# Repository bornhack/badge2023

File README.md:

# BornHack 2023 NFC Badges

With this years badges, we are taking a look at NFC. There will be two badges, one that is a tag (using the NXP NTAG I2C Plus chip), and another with an NFC reader (using NXP PN7150), that can also do card emulation.

The reader badge sports an RP2040 dual core Cortex M0+ microcontroller from Raspberry Pi and 16MB of Quad SPI flash for code and data files, to handle USB connection and general application control.

The reader badge will come with [CircuitPython](https://circuitpython.org/) preloaded, for a very low barrier of entry, all you need is a USB-C cable, and your favorite text editor and you're ready for NFC hacking.

## CircuitPython restore file

If you flash the board with something else and want to get back to CircuitPython:
Bring the badge into the UF2 bootloader. This is done by holding the BOOT button and pressing RESET or by holding BOOT while powering on.
The badge will then show up as a mass storage device called something like RP2-?. This is the built in bootloader.
Then simply copy [firmware.uf2](https://github.com/bornhack/badge2023/raw/main/firmware.uf2) from the root of this repository.
The badge will reboot, and you are then back to CircuitPython.

CircuitPython supported with this board is found in the [circuitpython branch](https://github.com/bornhack/badge2023/tree/circuitpython)

The original python files that was on the badge when handed out are in the [cp-init branch](https://github.com/bornhack/badge2023/tree/cp-init)

## Designed in KiCad v7

To open the project, you will need to install a recent release version or one of the nightly builds, KiCad v5 or v6 won't open this design. The [reader schematic as a PDF](https://github.com/bornhack/badge2023/raw/main/nfc_reader/nfc_reader_schematics.pdf) and the [tag schematic as a PDF](https://github.com/bornhack/badge2023/raw/main/nfc_card_emulation_large/nfc_card_emulation_large_schematics.pdf) are included for reference.

Main Components:

- [Raspberry Pi SoC RP2040 - low-cost, high-performance microcontroller device](https://www.raspberrypi.com/documentation/microcontrollers/rp2040.html)
    - [datasheet](https://datasheets.raspberrypi.com/rp2040/rp2040-datasheet.pdf)
    - [RP2040 SDK Manuel](https://www.raspberrypi.com/documentation/microcontrollers/c_sdk.html#sdk-setup)
    - [RP2040 SDK git repository](https://github.com/raspberrypi/pico-sdk)
- [NXP PN7150 - High-Performance NFC Controller with Integrated Firmware](https://www.nxp.com/products/rfid-nfc/nfc-hf/nfc-readers/high-performance-nfc-controller-with-integrated-firmware-for-smart-devices:PN7150)
    - [Datasheet](https://www.nxp.com/docs/en/data-sheet/PN7150.pdf)
    - [User Manual](https://www.nxp.com/docs/en/user-guide/UM10936.pdf)
- [W25Q128JV - 128M-bit Serial Flash Memory with uniform 4KB sectors and Dual/Quad SPI](https://www.winbond.com/hq/product/code-storage-flash-memory/serial-nor-flash/?__locale=en&partNo=W25Q128JV)
    - [datasheet](https://www.winbond.com/hq/support/documentation/downloadV2022.jsp?__locale=en&xmlPath=/support/resources/.content/item/DA00-W25Q128JV.html&level=1)
- [NXP NT3H2211W0FTT - NTAG I2C plus 2K, NFC Forum Type 2 Tag with I2C interface](https://www.nxp.com/part/NT3H2211W0FTT#/)
    - [datasheet](https://www.nxp.com/docs/en/data-sheet/NT3H2111_2211.pdf)

## Projects running on the badge

Feel free to submit a PR adding on to this list with your project that runs on the badge.

- _project name and link to more info_

## License

The hardware design of the `main` branch of this repository is released under the following license:

* the "Creative Commons Attribution-ShareAlike 4.0 International License"
  (CC BY-SA 4.0) full text of this license is included in the LICENSE file
  and a copy can also be found at
  [http://creativecommons.org/licenses/by-sa/4.0/](http://creativecommons.org/licenses/by-sa/4.0/)

The CircuitPython firmware of the `circuitpython` branch is released under the MIT license with smaller dependencies under other licenses as detailed in [its LICENSE](https://github.com/bornhack/badge2023/blob/circuitpython/LICENSE) and [LICENSE_MicroPython](https://github.com/bornhack/badge2023/blob/circuitpython/LICENSE_MicroPython) files.

The Python NFC demonstration application of the `cp-init` branch is released under the MIT license as detailed in its [LICENSE file](https://github.com/bornhack/badge2023/blob/cp-init/LICENSE).

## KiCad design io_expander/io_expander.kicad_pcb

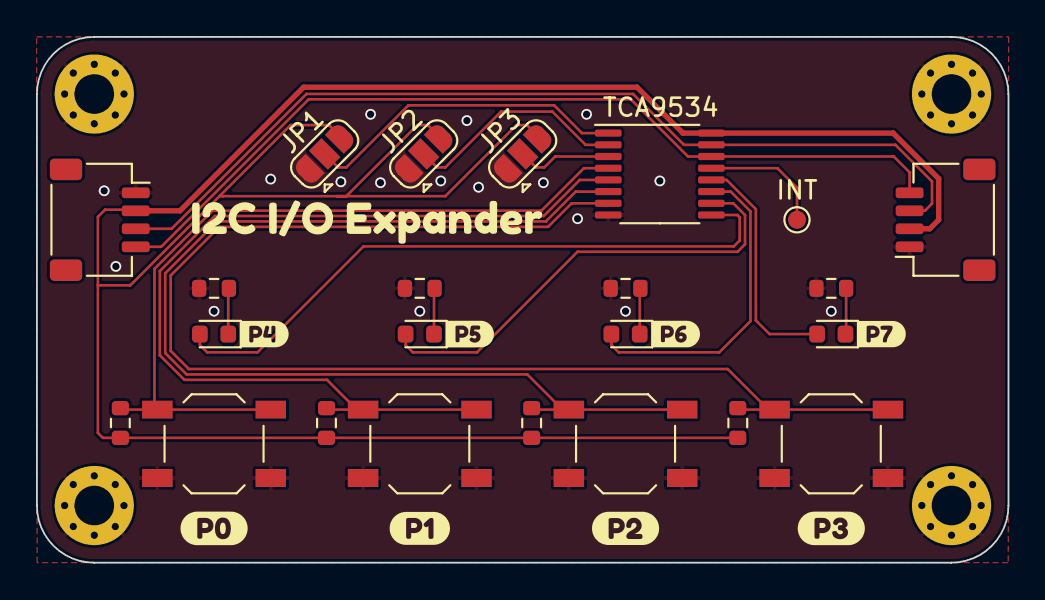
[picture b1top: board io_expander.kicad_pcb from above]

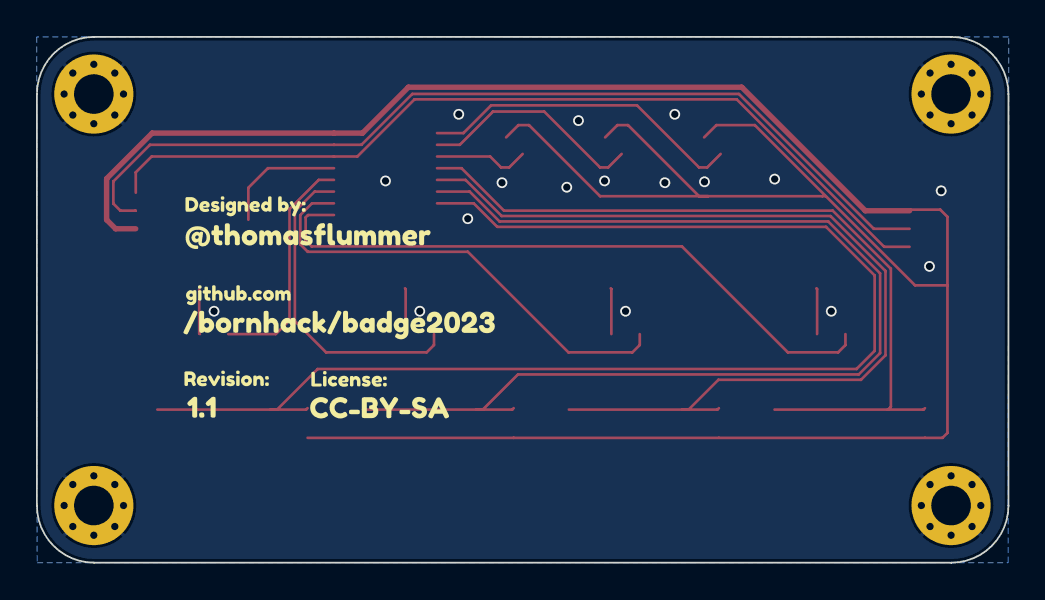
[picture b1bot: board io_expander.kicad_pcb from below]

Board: 2 copper layers, 54.0 x 29.2 mm, 40 parts (8 on the bottom side), 20 nets.

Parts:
D1, D2, D3, D4: LED; LED_0603_1608Metric
J1, J2: LCSC C145956; JST_SH_SM04B-SRSS-TB_1x04-1MP_P1.00mm_Horizontal
JP1, JP2, JP3: SolderJumper_3_Open; SolderJumper-3_P1.3mm_Open_RoundedPad1.0x1.5mm
R1, R2, R3, R4: 1k; R_0603_1608Metric
R5, R6, R7, R8: 10k; R_0603_1608Metric
SW1, SW2, SW3, SW4: TS5220A; SW_SPST_TL3342
TP1: INT; TestPoint_Pad_D1.0mm
U1: TCA9534; TSSOP-16_4.4x5mm_P0.65mm
kibuzzard-645C11AA: G***; kibuzzard-645C11AA
kibuzzard-645C104C: G***; kibuzzard-645C104C
kibuzzard-645C107E: G***; kibuzzard-645C107E
kibuzzard-645C118B: G***; kibuzzard-645C118B
kibuzzard-645C1150: G***; kibuzzard-645C1150
kibuzzard-652C0514: G***; kibuzzard-652C0514
kibuzzard-6495A71A: G***; kibuzzard-6495A71A
kibuzzard-6495A79F: G***; kibuzzard-6495A79F
kibuzzard-6495A738: G***; kibuzzard-6495A738
kibuzzard-6495A742: G***; kibuzzard-6495A742
kibuzzard-6495A748: G***; kibuzzard-6495A748
kibuzzard-6495A762: G***; kibuzzard-6495A762
kibuzzard-6495A791: G***; kibuzzard-6495A791
kibuzzard-6495A798: G***; kibuzzard-6495A798
kibuzzard-6495A825: G***; kibuzzard-6495A825
kibuzzard-64946969: G***; kibuzzard-64946969
kibuzzard-64946977: G***; kibuzzard-64946977

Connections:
/A0: JP1.2 (C), U1.1 (A0)
/A1: JP2.2 (C), U1.2 (A1)
/A2: JP3.2 (C), U1.3 (A2)
/SCL: J1.4, J2.4, U1.14 (SCL)
/SDA: J1.3, J2.3, U1.15 (SDA)
GND: J1.1, J2.1, JP1.1 (A), JP2.1 (A), JP3.1 (A), R1.2, R2.2, R3.2, R4.2, SW1.2 (B), SW2.2 (B), SW3.2 (B), SW4.2 (B), U1.8 (GND)
unnamed: D1.1 (K), R1.1
unnamed: D2.1 (K), R2.1
unnamed: D3.1 (K), R3.1
unnamed: D4.1 (K), R4.1
unnamed: TP1.1, U1.13 (~INT)
P0: R5.1, SW1.1 (A), U1.4 (P0)
P1: R6.1, SW2.1 (A), U1.5 (P1)
P2: R7.1, SW3.1 (A), U1.6 (P2)
P3: R8.1, SW4.1 (A), U1.7 (P3)
P4: D1.2 (A), U1.9 (P4)
P5: D2.2 (A), U1.10 (P5)
P6: D3.2 (A), U1.11 (P6)
P7: D4.2 (A), U1.12 (P7)
VCC: J1.2, J2.2, JP1.3 (B), JP2.3 (B), JP3.3 (B), R5.2, R6.2, R7.2, R8.2, U1.16 (VDD)

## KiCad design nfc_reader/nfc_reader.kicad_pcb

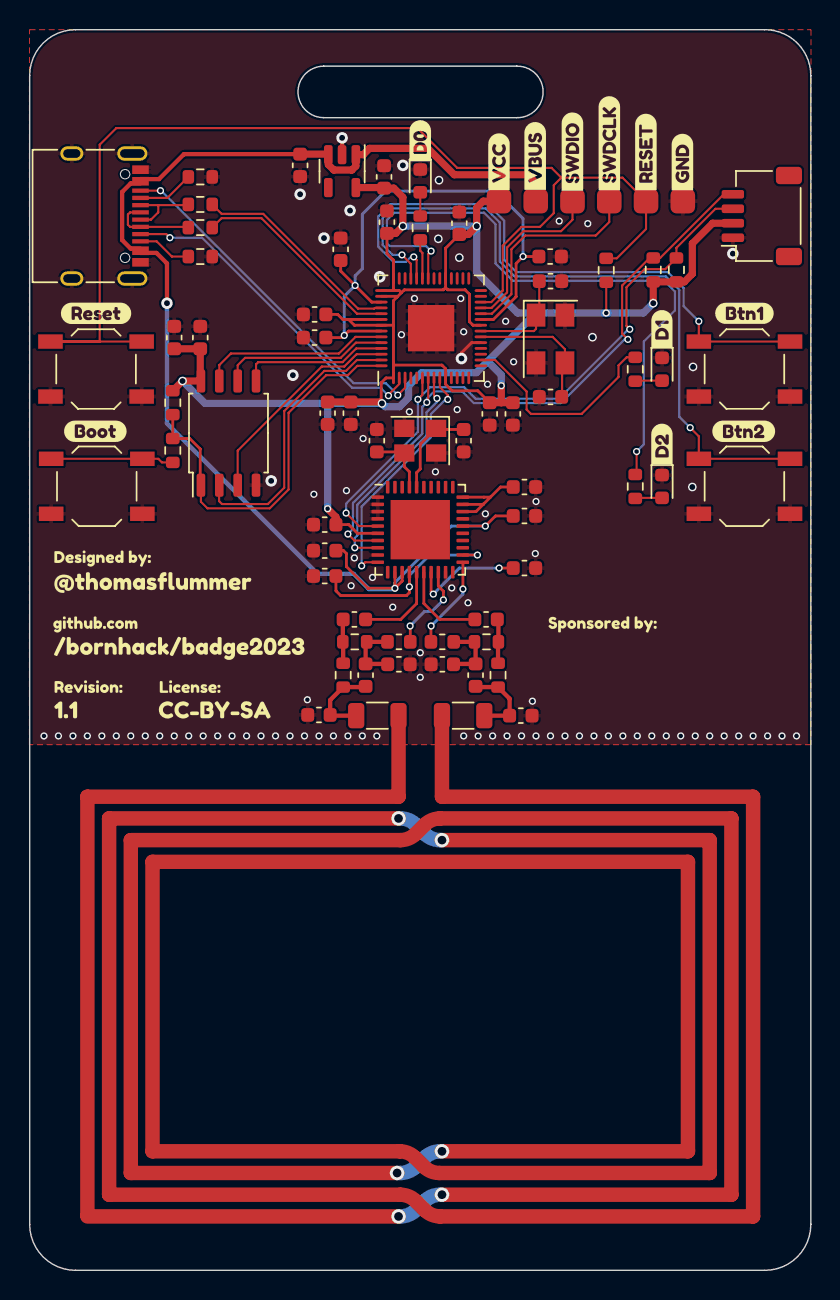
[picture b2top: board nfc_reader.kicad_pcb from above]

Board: 2 copper layers, 54.0 x 85.7 mm, 90 parts (0 on the bottom side), 52 nets.

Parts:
C1, C2, C3, C20, C22: 1uF; C_0603_1608Metric
C4, C6, C7, C8, C9, C10, C11, C13, C14, C18, C19: 100nF; C_0603_1608Metric
C5, C12, C17: 2.2uF; C_0603_1608Metric
C15, C16: 30pF; C_0603_1608Metric
C21: 4.7uF; C_0603_1608Metric
C23, C24: 10pF; C_0603_1608Metric
C25, C26: 1nF/16V; C_0603_1608Metric
C27, C28, C29, C30: 200pF/16V, NP0, 5%; C_0603_1608Metric
C31, C32: 27pF/50V, NP0, 2%; C_0603_1608Metric
D0, D1, D2: LED; LED_0603_1608Metric
J1: USB_C; USB_C_Receptacle_XKB_U262-16XN-4BVC11
J2: LCSC C145956; JST_SH_SM04B-SRSS-TB_1x04-1MP_P1.00mm_Horizontal
J3: DEBUG; PinHeader_1x06_P2.54mm_Vertical
L1, L2: 560nH, 5%; L_0603_1608Metric
R1, R2, R10, R11: 10k; R_0603_1608Metric
R3, R4, R9, R12, R17, R18: 1k; R_0603_1608Metric
R5, R6: R; R_0603_1608Metric
R7, R8: 5.1k; R_0603_1608Metric
R13, R14: 27R; R_0603_1608Metric
R15, R16: 2.00R 1%; R_1206_3216Metric
SW1, SW2, SW6, SW7: TS5220A; SW_SPST_TL3342
U1: HX9193-33GB; SOT-23-5
U3: PN7150B0HN/C11002Y; HVQFN-40-1EP_6x6mm_P0.5mm_EP4.1x4.1mm
U4: W25QXX128MBIT; SOIC-8_5.23x5.23mm_P1.27mm
U5: RP2040; QFN-56_EP_7x7_Pitch0.4mm
Y1: 12MHz, 20pF; Crystal_SMD_5032-4Pin_5.0x3.2mm
Y2: 27.12MHz, 10pF; Crystal_SMD_3225-4Pin_3.2x2.5mm
kibuzzard-645C11AA: G***; kibuzzard-645C11AA
kibuzzard-645C104C: G***; kibuzzard-645C104C
kibuzzard-645C107E: G***; kibuzzard-645C107E
kibuzzard-645C118B: G***; kibuzzard-645C118B
kibuzzard-645C1150: G***; kibuzzard-645C1150
kibuzzard-647C7A14: G***; kibuzzard-647C7A14
kibuzzard-647C89AC: G***; kibuzzard-647C89AC
kibuzzard-647C89B2: G***; kibuzzard-647C89B2
kibuzzard-647C8669: G***; kibuzzard-647C8669
kibuzzard-647C8670: G***; kibuzzard-647C8670
kibuzzard-647C8676: G***; kibuzzard-647C8676
kibuzzard-6457AB78: G***; kibuzzard-6457AB78
kibuzzard-6457ABA7: G***; kibuzzard-6457ABA7
kibuzzard-6457ABCE: G***; kibuzzard-6457ABCE
kibuzzard-6457ABE9: G***; kibuzzard-6457ABE9
kibuzzard-6457ABF7: G***; kibuzzard-6457ABF7
kibuzzard-6457AC2E: G***; kibuzzard-6457AC2E
kibuzzard-6457AC15: G***; kibuzzard-6457AC15
kibuzzard-6457AC22: G***; kibuzzard-6457AC22
kibuzzard-64945DE3: G***; kibuzzard-64945DE3
kibuzzard-64945DF1: G***; kibuzzard-64945DF1
kibuzzard-64946152: G***; kibuzzard-64946152

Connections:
+1V1: C12.1, C13.1, C14.1, U5.23 (DVDD), U5.45 (VREG_VOUT), U5.50 (DVDD)
/PN7150 reader/COIL: R15.2, R16.2
/PN7150 reader/IRQ: U3.8 (IRQ), U5.8 (GPIO6)
/PN7150 reader/VEN: U3.10 (VEN), U5.9 (GPIO7)
/SCL: J2.4, R1.2, U3.7 (I2CSCL), U5.7 (GPIO5)
/SDA: J2.3, R2.2, U3.5 (I2CSDA), U5.6 (GPIO4)
/VUSB: C1.1, C19.1, C21.1, J1.A4 (VBUS), J1.A9 (VBUS), J1.B4 (VBUS), J1.B9 (VBUS), J3.2, U1.1 (VIN), U1.3 (EN), U3.12 (VBAT2), U3.13 (VBAT1), U3.26 (VBAT)
/rp2040/A0: SW1.1 (A), U5.38 (GPIO26)
/rp2040/A1: SW2.1 (A), U5.39 (GPIO27)
/rp2040/D+: R14.2, U5.47 (USB_D+)
/rp2040/D-: R13.2, U5.46 (USB_D-)
/rp2040/PWM0: R17.2, U5.16 (GPIO13)
/rp2040/PWM1/AUD_MCLK: R18.2, U5.36 (GPIO24)
/rp2040/QSPI-0: U4.5 (DI(IO0)), U5.53 (QSPI_SD0)
/rp2040/QSPI-1: U4.2 (DO(IO1)), U5.55 (QSPI_SD1)
/rp2040/QSPI-2: U4.3 (IO2), U5.54 (QSPI_SD2)
/rp2040/QSPI-3: U4.7 (IO3), U5.51 (QSPI_SD3)
/rp2040/QSPI-CLK: U4.6 (CLK), U5.52 (QSPI_SCLK)
/rp2040/QSPI-~CS: R9.2, R11.2, U4.1 (~CS), U5.56 (~QSPI_CS)
/rp2040/SBU1: J1.A8 (SBU1), U5.2 (GPIO0)
/rp2040/SBU2: J1.B8 (SBU2), U5.3 (GPIO1)
/rp2040/SWDCLK: J3.4, U5.24 (SWCLK)
/rp2040/SWDIO: J3.3, U5.25 (SWDIO)
/rp2040/USB_D+: J1.A6 (D+), J1.B6 (D+), R14.1
/rp2040/USB_D-: J1.A7 (D-), J1.B7 (D-), R13.1
/rp2040/~BOOT: R9.1, SW7.2 (B)
/rp2040/~RESET: J3.5, R10.2, SW6.2 (B), U5.26 (RUN)
GND: C1.2, C2.2, C3.2, C4.2, C5.2, C6.2, C7.2, C8.2, C9.2, C10.2, C11.2, C12.2, C13.2, C14.2, C15.1, C16.1, C17.2, C18.2, C19.2, C20.2, C21.2, C22.2, C23.2, C24.2, C27.2, C28.1, C29.2, C30.1, D0.1 (K), D1.1 (K), D2.1 (K), J1.A1 (GND), J1.A12 (GND), J1.B1 (GND), J1.B12 (GND), J1.S1 (SHIELD), J2.1, J3.6, R7.1, R8.1, SW1.2 (B), SW2.2 (B), SW6.1 (A), SW7.1 (A), U1.2 (GND), U3.1 (I2CADR0), U3.2 (i.c.), U3.3 (I2CADR1), U3.4 (VSS(PAD)), U3.9 (VSS), U3.19 (VSS(TX)), U3.27 (VSS), U4.4 (GND), U5.19 (TESTEN), U5.57 (GND), Y1.2, Y1.4, Y2.2, Y2.4
unnamed: C25.2, R4.2, R5.1
unnamed: C26.1, R3.1, R6.1
unnamed: C27.1, C31.1, L1.2, R3.2
unnamed: C28.2, C32.1, L2.2, R4.1
unnamed: C29.1, C31.2, R6.2, R15.1
unnamed: C30.2, C32.2, R5.2, R16.1
unnamed: D0.2 (A), R12.1
unnamed: D1.2 (A), R17.1
unnamed: D2.2 (A), R18.1
unnamed: J1.A5 (CC1), R7.2
unnamed: J1.B5 (CC2), R8.2
unnamed: C24.1, U3.36 (NFC_CLK_XTAL1), Y2.1
unnamed: C23.1, U3.37 (NFC_CLK_XTAL2), Y2.3
unnamed: C25.1, U3.15 (RXN)
unnamed: C26.2, U3.16 (RXP)
unnamed: L1.1, U3.21 (TX1)
unnamed: L2.1, U3.18 (TX2)
unnamed: C4.1, U3.17 (VCC(MID))
unnamed: C2.1, U3.14 (VCC(TX)), U3.22 (VDD(TX_IN))
unnamed: C20.1, U3.28 (VDDA), U3.29 (VDD), U3.30 (VDDD)
unnamed: R12.2, U5.37 (GPIO25)
unnamed: C15.2, U5.20 (XIN), Y1.3
unnamed: C16.2, U5.21 (XOUT), Y1.1
VCC: C3.1, C5.1, C6.1, C7.1, C8.1, C9.1, C10.1, C11.1, C17.1, C18.1, C22.1, J2.2, J3.1, R1.1, R2.1, R10.1, R11.1, U1.5 (VOUT), U3.6 (VDD(PAD)), U4.8 (VCC), U5.1 (IOVDD), U5.10 (IOVDD), U5.22 (IOVDD), U5.33 (IOVDD), U5.42 (IOVDD), U5.43 (ADC_AVDD), U5.44 (VREG_VIN), U5.48 (USB_VDD), U5.49 (IOVDD)

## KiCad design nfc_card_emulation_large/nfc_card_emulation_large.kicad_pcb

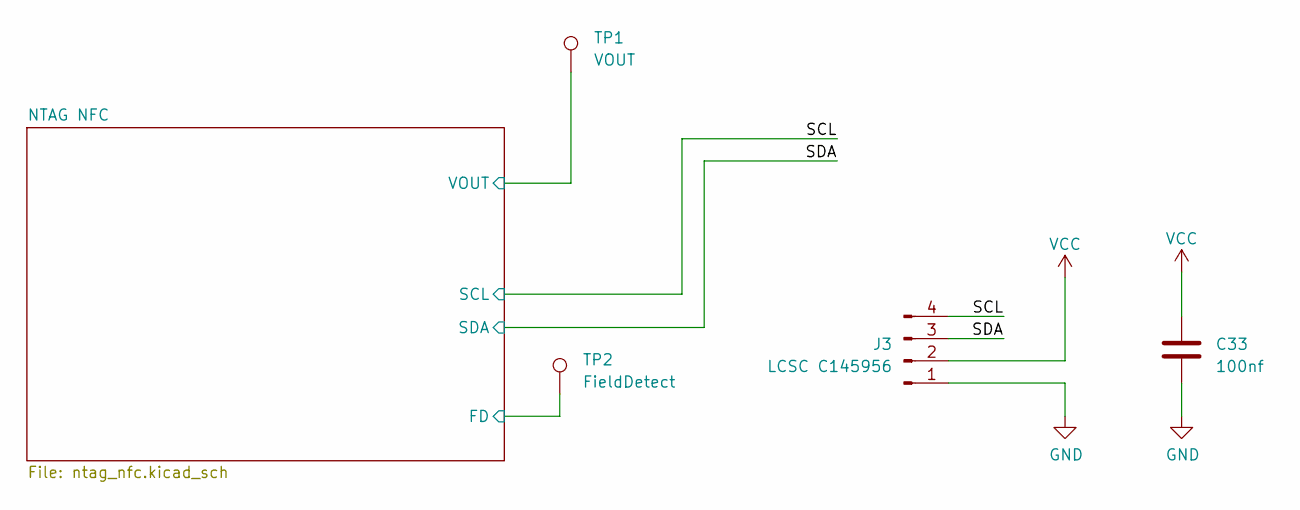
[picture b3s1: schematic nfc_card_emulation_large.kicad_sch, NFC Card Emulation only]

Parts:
C33: 100nf; C_0603_1608Metric
J3: LCSC C145956; JST_SH_SM04B-SRSS-TB_1x04-1MP_P1.00mm_Horizontal
TP1: VOUT; TestPoint_Pad_D1.0mm
TP2: FieldDetect; TestPoint_Pad_D1.0mm

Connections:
/NTAG NFC/FD: TP2.1; also elsewhere on the board
/NTAG NFC/VOUT: TP1.1; also elsewhere on the board
/SCL: J3.4; also elsewhere on the board
/SDA: J3.3; also elsewhere on the board
GND: C33.2, J3.1; also elsewhere on the board
VCC: C33.1, J3.2; also elsewhere on the board

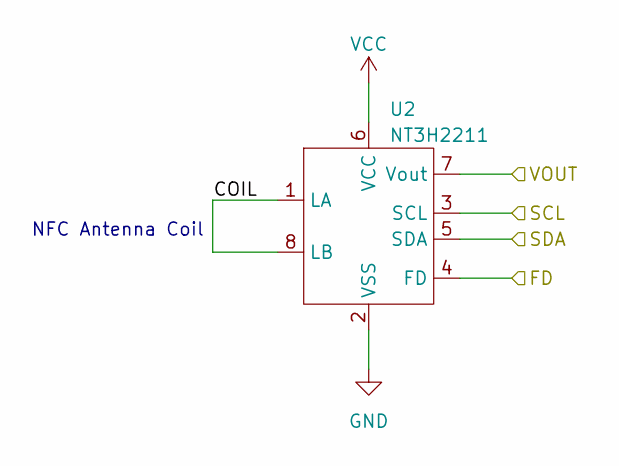
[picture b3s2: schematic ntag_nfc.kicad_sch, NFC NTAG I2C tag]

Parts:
U2: NT3H2211; TSSOP-8_3x3mm_P0.65mm

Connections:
/NTAG NFC/COIL: U2.1 (LA), U2.8 (LB)
/NTAG NFC/FD: U2.4 (FD); also elsewhere on the board
/NTAG NFC/VOUT: U2.7 (Vout); also elsewhere on the board
/SCL: U2.3 (SCL); also elsewhere on the board
/SDA: U2.5 (SDA); also elsewhere on the board
GND: U2.2 (VSS); also elsewhere on the board
VCC: U2.6 (VCC); also elsewhere on the board

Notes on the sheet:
NFC Antenna Coil

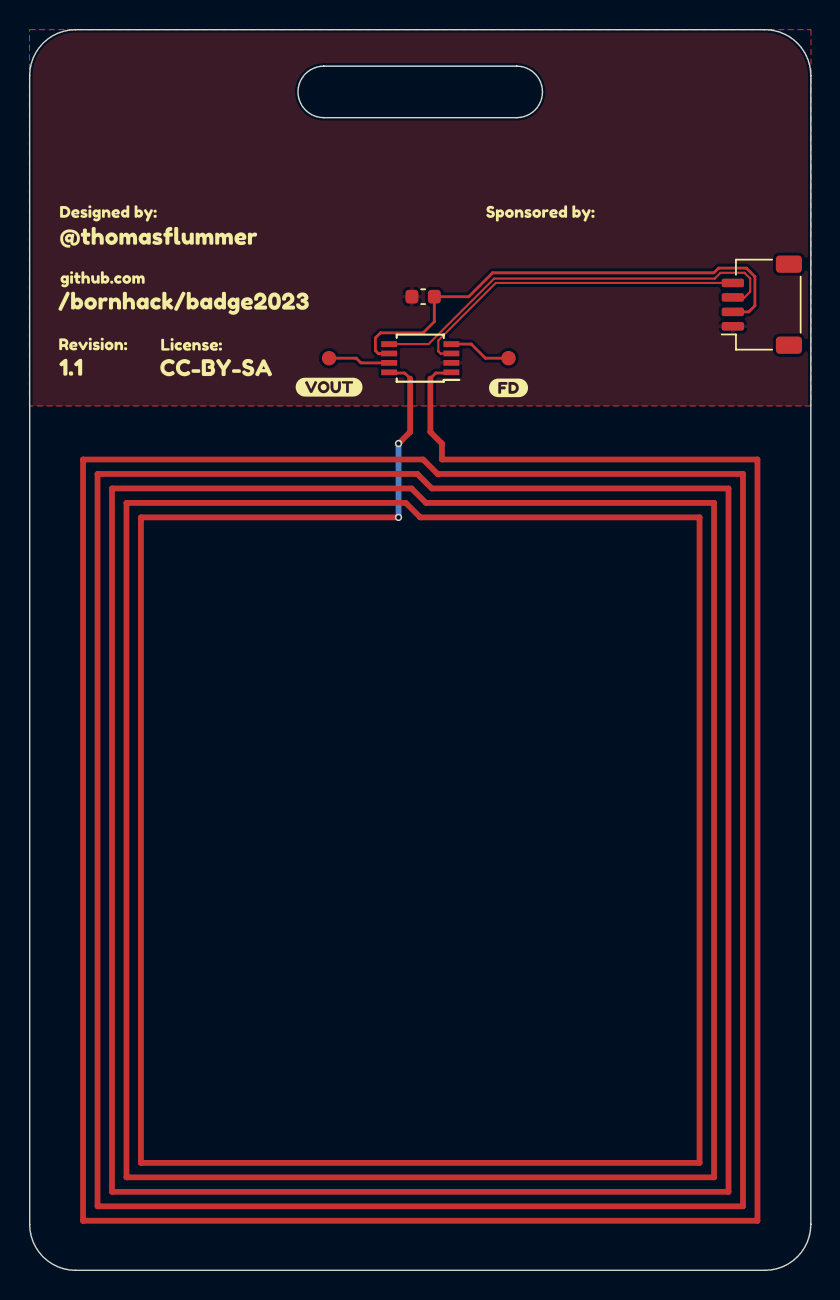
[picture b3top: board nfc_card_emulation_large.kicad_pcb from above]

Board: 2 copper layers, 54.0 x 85.7 mm, 16 parts (0 on the bottom side), 7 nets.

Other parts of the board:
kibuzzard-645C11AA: G***; kibuzzard-645C11AA
kibuzzard-645C104C: G***; kibuzzard-645C104C
kibuzzard-645C107E: G***; kibuzzard-645C107E
kibuzzard-645C118B: G***; kibuzzard-645C118B
kibuzzard-645C1150: G***; kibuzzard-645C1150
kibuzzard-647C9608: G***; kibuzzard-647C9608
kibuzzard-649468CC: G***; kibuzzard-649468CC
kibuzzard-649468E2: G***; kibuzzard-649468E2
kibuzzard-649469D3: G***; kibuzzard-649469D3
kibuzzard-64946969: G***; kibuzzard-64946969
kibuzzard-64946977: G***; kibuzzard-64946977

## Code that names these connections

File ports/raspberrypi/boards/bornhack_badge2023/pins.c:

#include "shared-bindings/board/__init__.h"

STATIC const mp_rom_map_elem_t board_module_globals_table[] = {
    CIRCUITPYTHON_BOARD_DICT_STANDARD_ITEMS

    { MP_ROM_QSTR(MP_QSTR_SDA),  MP_ROM_PTR(&pin_GPIO4)  },
    { MP_ROM_QSTR(MP_QSTR_SCL),  MP_ROM_PTR(&pin_GPIO5)  },
    { MP_ROM_QSTR(MP_QSTR_IRQ),  MP_ROM_PTR(&pin_GPIO6)  },
    { MP_ROM_QSTR(MP_QSTR_VEN),  MP_ROM_PTR(&pin_GPIO7)  },
    { MP_ROM_QSTR(MP_QSTR_D1),   MP_ROM_PTR(&pin_GPIO13) },
    { MP_ROM_QSTR(MP_QSTR_D2),   MP_ROM_PTR(&pin_GPIO24) },
    { MP_ROM_QSTR(MP_QSTR_D0),   MP_ROM_PTR(&pin_GPIO25) },
    { MP_ROM_QSTR(MP_QSTR_LED),  MP_ROM_PTR(&pin_GPIO25) },
    { MP_ROM_QSTR(MP_QSTR_BTN1), MP_ROM_PTR(&pin_GPIO26) },
    { MP_ROM_QSTR(MP_QSTR_BTN2), MP_ROM_PTR(&pin_GPIO27) },

    { MP_ROM_QSTR(MP_QSTR_I2C), MP_ROM_PTR(&board_i2c_obj) },
};
MP_DEFINE_CONST_DICT(board_module_globals, board_module_globals_table);

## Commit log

2023-06-23 Added front artwork to nfc_card_emulation_large
    Also created BOM and pos files
2023-06-23 Added front artwork to nfc_reader
    Also
    - Fixed error with missing power to PN7150 radio
    - Added two buttons and two LEDs
    - Moved things around a little
    - Updated BOM and created pos file
2023-06-23 Added I/O Expander board
2023-06-25 Added schematics as PDF files
2023-07-12 Add readme
2023-07-16 README.md: trivial typo fix
2023-08-01 Add BornHack Badge 2023
2023-08-01 Added link to circuitpython branch
2023-08-05 Added circuitpython firmware.uf2 binary for restore
2023-08-05 Update README.md
    Some language adjustments and formatting changes
2023-08-05 Add list of main components and doc. links
2023-08-05 Add software license information to README
2023-08-06 Added option to read the chip sectors
2023-08-07 Recognize more types of packages
2023-08-07 Reuse buffer for tag command
2023-10-15 Fixed I2C I/O Expander design
    - Added pullup resistors on buttons
    - Changed to 3 pin solder jumpers, to allow address pins to be tied to either VCC or GND
2023-10-15 Updated Interactive BOM for I2C I/O Expander
